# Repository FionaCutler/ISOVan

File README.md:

# People Mover PCB
A dual ISO Enter PCB designed around Minivan case compatibility

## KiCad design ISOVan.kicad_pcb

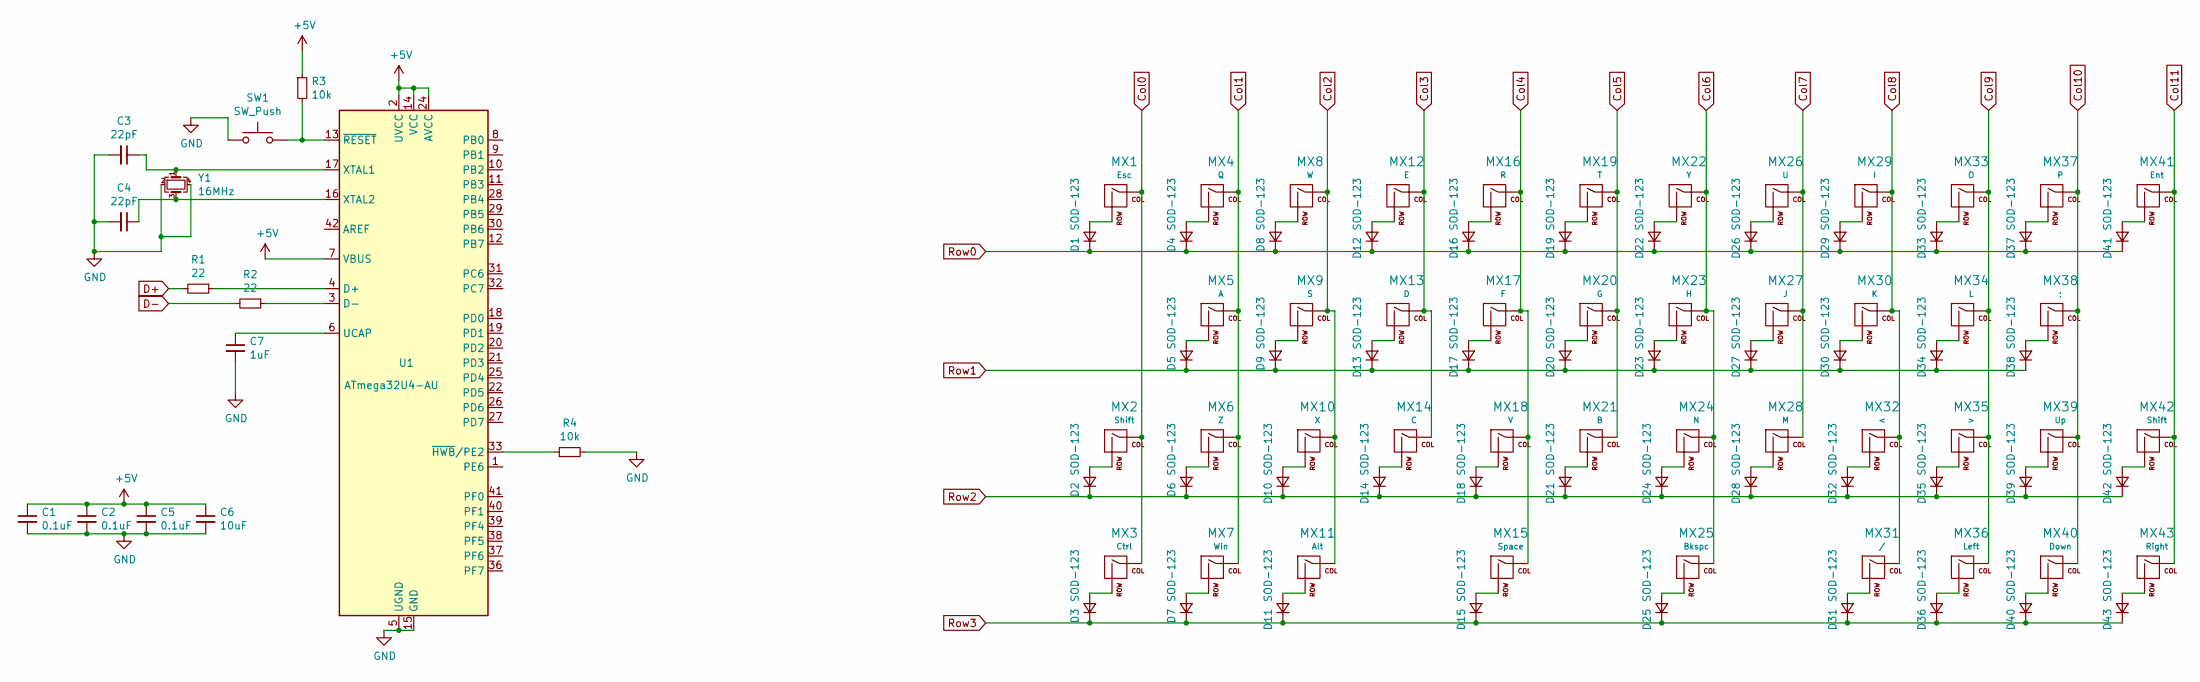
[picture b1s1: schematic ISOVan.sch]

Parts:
C1, C2, C5: 0.1uF; C_0805_2012Metric
C3, C4: 22pF; C_0805_2012Metric
C6: 10uF; C_0805_2012Metric
C7: 1uF; C_0805_2012Metric
D1, D2, D3, D4, D5, D6, D7, D8, D9, D10, D11, D12, D13, D14, D15, D16, D17, D18, D19, D20, D21, D22, D23, D24, D25, D26, D27, D28, D29, D30, D31, D32, D33, D34, D35, D36, D37, D38, D39, D40, D41, D42, D43: SOD-123; D_SOD-123
MX1: Esc; MXOnly-ISO-ReversedStabilizers
MX2: Shift; MXOnly-1.75U-NoLED
MX3: Ctrl; MXOnly-1.5U-NoLED
MX4: Q; MXOnly-1U-NoLED
MX5: A; MXOnly-1U-NoLED
MX6: Z; MXOnly-1U-NoLED
MX7: Win; MXOnly-1.25U-NoLED
MX8: W; MXOnly-1U-NoLED
MX9: S; MXOnly-1U-NoLED
MX10: X; MXOnly-1U-NoLED
MX11: Alt; MXOnly-1.25U-NoLED
MX12: E; MXOnly-1U-NoLED
MX13: D; MXOnly-1U-NoLED
MX14: C; MXOnly-1U-NoLED
MX15: Space; MXOnly-2.25U-ReversedStabilizers-NoLED
MX16: R; MXOnly-1U-NoLED
MX17: F; MXOnly-1U-NoLED
MX18: V; MXOnly-1U-NoLED
MX19: T; MXOnly-1U-NoLED
MX20: G; MXOnly-1U-NoLED
MX21: B; MXOnly-1U-NoLED
MX22: Y; MXOnly-1U-NoLED
MX23: H; MXOnly-1U-NoLED
MX24: N; MXOnly-1U-NoLED
MX25: Bkspc; MXOnly-2U-FLIPPED-ReversedStabilizers
MX26: U; MXOnly-1U-NoLED
MX27: J; MXOnly-1U-NoLED
MX28: M; MXOnly-1U-NoLED
MX29: I; MXOnly-1U-NoLED
MX30: K; MXOnly-1U-NoLED
MX31: /; MXOnly-1.5U-NoLED
MX32: <; MXOnly-1U-NoLED
MX33: O; MXOnly-1U-NoLED
MX34: L; MXOnly-1U-NoLED
MX35: >; MXOnly-1U-NoLED
MX36: Left; MXOnly-1U-NoLED
MX37: P; MXOnly-1U-NoLED
MX38: ;; MXOnly-1U-NoLED
MX39: Up; MXOnly-1U-NoLED
MX40: Down; MXOnly-1U-NoLED
MX41: Ent; MXOnly-ISO-ReversedStabilizers
MX42: Shift; MXOnly-1U-NoLED
MX43: Right; MXOnly-1U-NoLED
R1, R2: 22; R_0805_2012Metric
R3, R4: 10k; R_0805_2012Metric
SW1: SW_Push; SKQG-1155865
U1: ATmega32U4-AU; TQFP-44_10x10mm_P0.8mm
Y1: 16MHz; Crystal_SMD_3225-4Pin_3.2x2.5mm

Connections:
+5V: C1.1, C2.1, C5.1, C6.1, R3.1, U1.2 (UVCC), U1.7 (VBUS), U1.14 (VCC), U1.24 (AVCC), U1.34 (VCC), U1.44 (AVCC)
Col0: MX1.1 (COL), MX2.1 (COL), MX3.1 (COL)
Col1: MX4.1 (COL), MX5.1 (COL), MX6.1 (COL), MX7.1 (COL)
Col2: MX8.1 (COL), MX9.1 (COL), MX10.1 (COL), MX11.1 (COL)
Col3: MX12.1 (COL), MX13.1 (COL), MX14.1 (COL)
Col4: MX15.1 (COL), MX16.1 (COL), MX17.1 (COL), MX18.1 (COL)
Col5: MX19.1 (COL), MX20.1 (COL), MX21.1 (COL)
Col6: MX22.1 (COL), MX23.1 (COL), MX24.1 (COL), MX25.1 (COL)
Col7: MX26.1 (COL), MX27.1 (COL), MX28.1 (COL)
Col8: MX29.1 (COL), MX30.1 (COL), MX31.1 (COL), MX32.1 (COL)
Col9: MX33.1 (COL), MX34.1 (COL), MX35.1 (COL), MX36.1 (COL)
Col10: MX37.1 (COL), MX38.1 (COL), MX39.1 (COL), MX40.1 (COL)
Col11: MX41.1 (COL), MX42.1 (COL), MX43.1 (COL)
GND: C1.2, C2.2, C3.2, C4.2, C5.2, C6.2, C7.2, R4.2, SW1.1, U1.5 (UGND), U1.15 (GND), U1.23 (GND), U1.35 (GND), U1.43 (GND), Y1.2, Y1.4
unnamed: C3.1, U1.17 (XTAL1), Y1.1
unnamed: C4.1, U1.16 (XTAL2), Y1.3
unnamed: C7.1, U1.6 (UCAP)
unnamed: D1.2 (A), MX1.2 (ROW)
unnamed: D2.2 (A), MX2.2 (ROW)
unnamed: D3.2 (A), MX3.2 (ROW)
unnamed: D4.2 (A), MX4.2 (ROW)
unnamed: D5.2 (A), MX5.2 (ROW)
unnamed: D6.2 (A), MX6.2 (ROW)
unnamed: D7.2 (A), MX7.2 (ROW)
unnamed: D8.2 (A), MX8.2 (ROW)
unnamed: D9.2 (A), MX9.2 (ROW)
unnamed: D10.2 (A), MX10.2 (ROW)
unnamed: D11.2 (A), MX11.2 (ROW)
unnamed: D12.2 (A), MX12.2 (ROW)
unnamed: D13.2 (A), MX13.2 (ROW)
unnamed: D14.2 (A), MX14.2 (ROW)
unnamed: D15.2 (A), MX15.2 (ROW)
unnamed: D16.2 (A), MX16.2 (ROW)
unnamed: D17.2 (A), MX17.2 (ROW)
unnamed: D18.2 (A), MX18.2 (ROW)
unnamed: D19.2 (A), MX19.2 (ROW)
unnamed: D20.2 (A), MX20.2 (ROW)
unnamed: D21.2 (A), MX21.2 (ROW)
unnamed: D22.2 (A), MX22.2 (ROW)
unnamed: D23.2 (A), MX23.2 (ROW)
unnamed: D24.2 (A), MX24.2 (ROW)
unnamed: D25.2 (A), MX25.2 (ROW)
unnamed: D26.2 (A), MX26.2 (ROW)
unnamed: D27.2 (A), MX27.2 (ROW)
unnamed: D28.2 (A), MX28.2 (ROW)
unnamed: D29.2 (A), MX29.2 (ROW)
unnamed: D30.2 (A), MX30.2 (ROW)
unnamed: D31.2 (A), MX31.2 (ROW)
unnamed: D32.2 (A), MX32.2 (ROW)
unnamed: D33.2 (A), MX33.2 (ROW)
unnamed: D34.2 (A), MX34.2 (ROW)
unnamed: D35.2 (A), MX35.2 (ROW)
unnamed: D36.2 (A), MX36.2 (ROW)
unnamed: D37.2 (A), MX37.2 (ROW)
unnamed: D38.2 (A), MX38.2 (ROW)
unnamed: D39.2 (A), MX39.2 (ROW)
unnamed: D40.2 (A), MX40.2 (ROW)
unnamed: D41.2 (A), MX41.2 (ROW)
unnamed: D42.2 (A), MX42.2 (ROW)
unnamed: D43.2 (A), MX43.2 (ROW)
unnamed: R1.1, U1.4 (D+)
unnamed: R2.1, U1.3 (D-)
unnamed: R3.2, SW1.2, U1.13 (~RESET)
unnamed: R4.1, U1.33 (~HWB~/PE2)
Row0: D1.1 (K), D4.1 (K), D8.1 (K), D12.1 (K), D16.1 (K), D19.1 (K), D22.1 (K), D26.1 (K), D29.1 (K), D33.1 (K), D37.1 (K), D41.1 (K)
Row1: D5.1 (K), D9.1 (K), D13.1 (K), D17.1 (K), D20.1 (K), D23.1 (K), D27.1 (K), D30.1 (K), D34.1 (K), D38.1 (K)
Row2: D2.1 (K), D6.1 (K), D10.1 (K), D14.1 (K), D18.1 (K), D21.1 (K), D24.1 (K), D28.1 (K), D32.1 (K), D35.1 (K), D39.1 (K), D42.1 (K)
Row3: D3.1 (K), D7.1 (K), D11.1 (K), D15.1 (K), D25.1 (K), D31.1 (K), D36.1 (K), D40.1 (K), D43.1 (K)

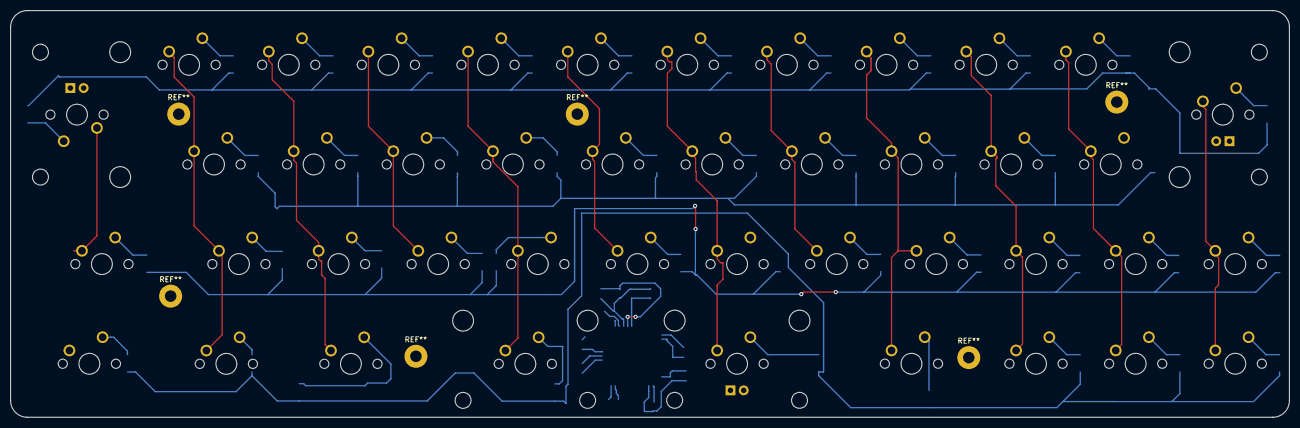
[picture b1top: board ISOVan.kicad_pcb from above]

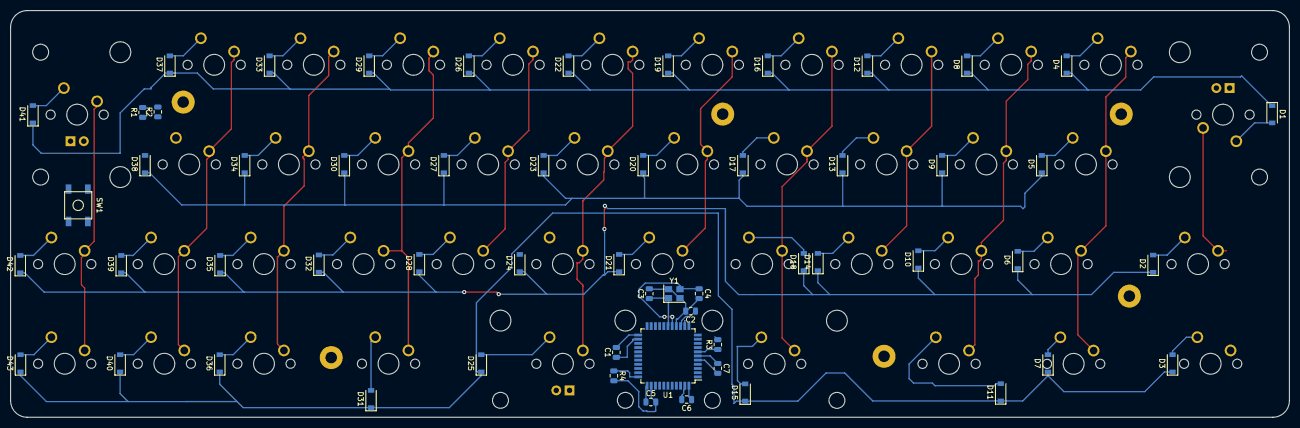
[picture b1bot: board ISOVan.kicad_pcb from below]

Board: 2 copper layers, 244.5 x 77.8 mm, 100 parts (57 on the bottom side), 68 nets.

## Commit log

2019-12-10 Aadd submodules
2019-12-10 complete microcontroller schematic
2019-12-10 start matrix
2019-12-10 Finish matrix
2019-12-11 assign footprints and make layout
2019-12-11 place components
2019-12-11 place screw holes
2019-12-12 new layout
2019-12-18 Route matrix and change layout again
2019-12-20 Route
2019-12-22 Route all but USB port
